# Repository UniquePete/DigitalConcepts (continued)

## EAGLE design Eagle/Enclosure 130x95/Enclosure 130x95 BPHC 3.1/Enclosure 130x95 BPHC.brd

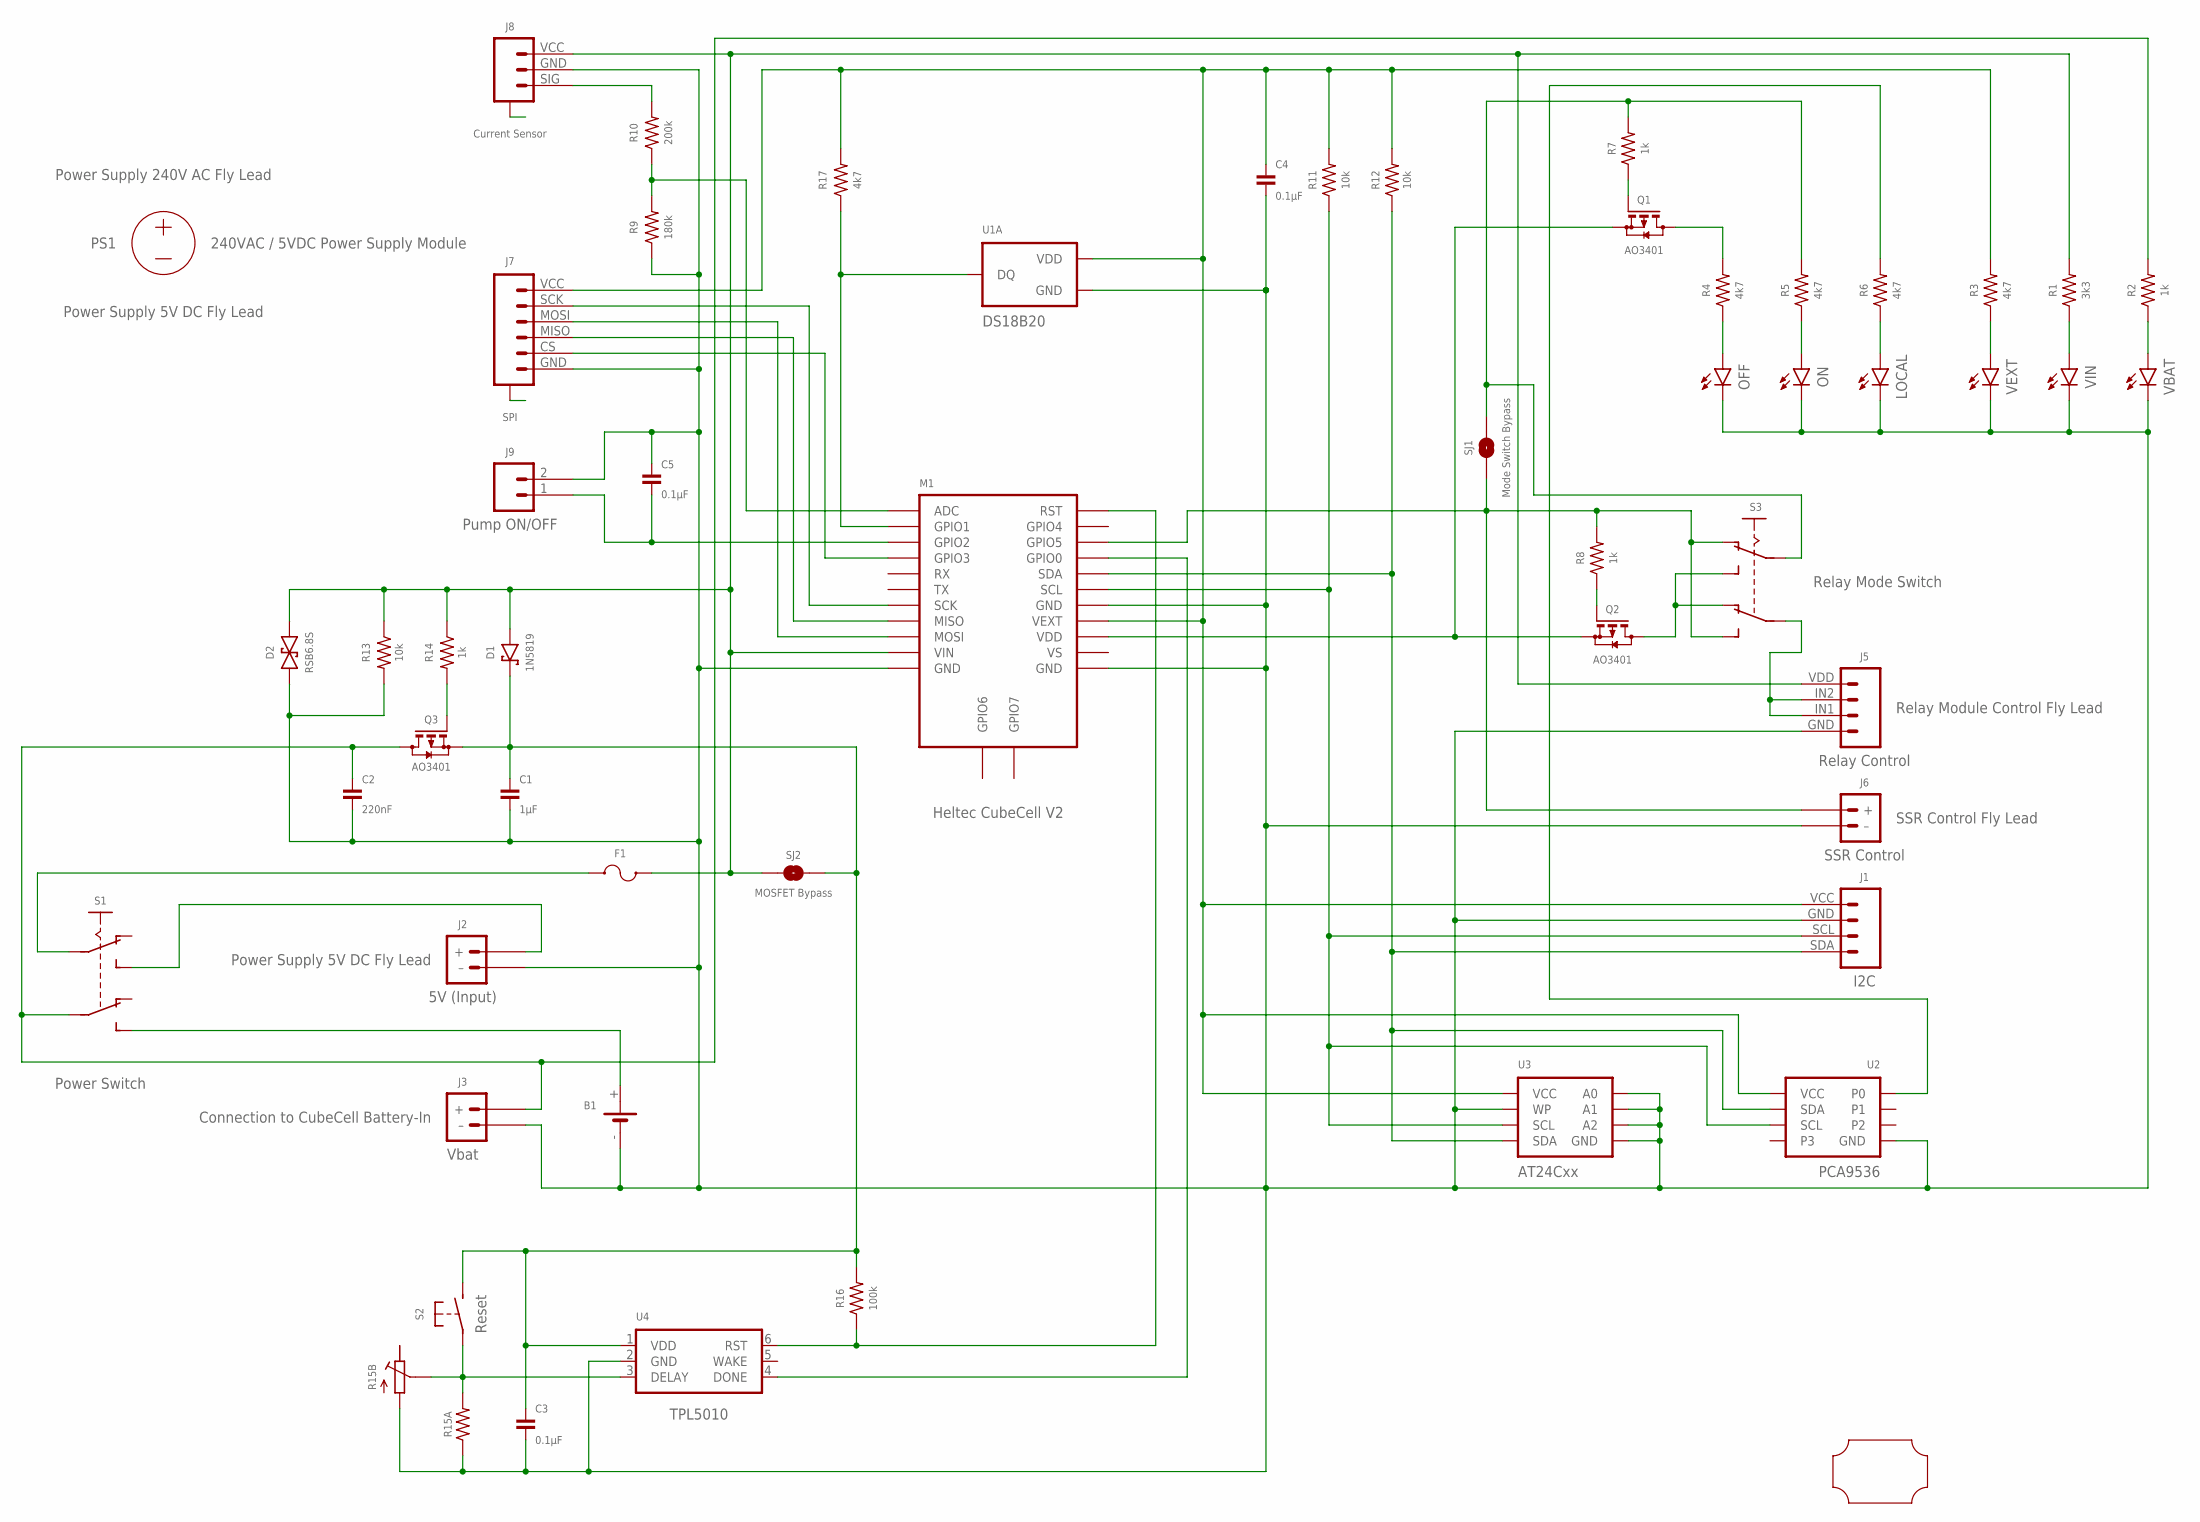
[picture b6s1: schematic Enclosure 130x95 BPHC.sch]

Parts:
B1: BATTERY-HOLDER-14500(AA); BATTERY-14500
C1: 1µF; C0805
C2: 220nF; C0805
C3, C4, C5: 0.1µF; C0805
D1: 1N5819; SOD-123
D2: RSB6.8S; VMD2
F1: Fuse; F0805
J1: I2C; CONN_04-I2C
J2: 5V (Input); JST-PH2.0-2-VERTICAL-POWER
J3: Vbat; JST-GH1.25-2-HORIZONTAL
J5: Relay Control; JST-PH2.0-4-HORIZONTAL-RELAY
J6: SSR Control; JST-PH2.0-2-HORIZONTAL-POWER
J7: SPI; JST-SH1.0-6-HORIZONTAL-SPI
J8: Current Sensor; JST-SH1.0-3-HORIZONTAL-SIG
J9: Pump ON/OFF; CONN_02-GENERIC
LOCAL: LEDCHIP-LED0805; CHIP-LED0805
M1: Heltec CubeCell V2; HELTEC-CUBECELL
OFF: LEDCHIP-LED0805; CHIP-LED0805
ON: LEDCHIP-LED0805; CHIP-LED0805
PCB1: PCB-OUTLINE-130X95-HALF-TOP; PROTO-130X95-OUTLINE-HALF-TOP
PS1: 240VAC / 5VDC Power Supply Module; AC_DC_POWER_SUPPLY
Q1, Q2, Q3: AO3401; SOT-23
R1: 3k3; R0805
R2, R7, R8, R14: 1k; R0805
R3, R4, R5, R6, R17: 4k7; R0805
R9: 180k; R0805
R10: 200k; R0805
R11, R12, R13: 10k; R0805
R15A: RESISTORR0805; R0805
R15B: RESISTOR-TRIMM-33; RTRIM3*3
R16: 100k; R0805
S1: Power Switch; SWITCH-DPDT-PTH
S2: Reset; SWITCH-2-PAD
S3: Relay Mode Switch; SWITCH-DPDT-SMD
SJ1: Mode Switch Bypass; SJ
SJ2: MOSFET Bypass; SJ
U1A: DS18B20; TO-92
U2: PCA9536; SOP-8
U3: AT24Cxx; SOP-8
U4: TPL5010; SOT-23-6
VBAT: LEDCHIP-LED0805; CHIP-LED0805
VEXT: LEDCHIP-LED0805; CHIP-LED0805
VIN: LEDCHIP-LED0805; CHIP-LED0805

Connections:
A6: J8.A@1 (A), J8.A@3 (A)
A8: J7.A@1 (A), J7.A@6 (A)
GND: B1.-, C1.2, C2.2, C3.2, C4.2, C5.1, D2.P$2 (2), J1.GND (2), J2.- (–), J3.- (–), J5.GND (4), J6.- (–), J7.GND (1), J8.GND (2), J9.2, LOCAL.C, M1.GND@11 (GND), M1.GND@14 (GND), M1.GND@18 (GND), OFF.C, ON.C, R9.1, R13.2, R15A.1, R15B.1 (A), U1A.1 (GND), U2.4 (GND), U3.1 (A0), U3.2 (A1), U3.3 (A2), U3.4 (GND), U3.7 (WP), U4.2 (GND), VBAT.C, VEXT.C, VIN.C
unnamed: R6.2, U2.1 (P0)
unnamed: B1.+, S1.P$6 (S2)
unnamed: C5.2, J9.1, M1.GPIO2
unnamed: C4.1, J1.VCC (1), J7.VCC (6), M1.VEXT, R3.2, R11.2, R12.2, R17.2, U1A.3 (VDD), U2.8 (VCC), U3.8 (VCC)
unnamed: J1.SDA (4), M1.SDA, R12.1, U2.7 (SDA), U3.5 (SDA)
unnamed: C1.1, C3.1, D1.C, Q3.2 (S), R16.2, S2.P$2 (S), SJ2.2, U4.1 (VDD)
unnamed: J6.+, M1.GPIO5, R8.2, S3.P$1 (O1), S3.P$6 (S2), SJ1.1
unnamed: M1.GPIO1, R17.1, U1A.2 (DQ)
unnamed: J1.SCL (3), M1.SCL, R11.1, U2.6 (SCL), U3.6 (SCL)
unnamed: R2.1, VBAT.A
unnamed: M1.GPIO0, U4.4 (DONE)
unnamed: OFF.A, R4.1
unnamed: R1.1, VIN.A
unnamed: R3.1, VEXT.A
unnamed: F1.2, S1.P$2 (P1)
unnamed: J2.+, S1.P$3 (S1)
unnamed: Q1.3 (D), R4.2
unnamed: M1.ADC, R9.2, R10.1
unnamed: ON.A, R5.1
unnamed: LOCAL.A, R6.1
unnamed: D1.A, D2.P$1 (1), F1.1, J5.VDD (1), J8.VCC (3), M1.VIN, R1.2, R13.1, R14.1, SJ2.1
unnamed: Q1.1 (G), R7.1
unnamed: Q2.3 (D), S3.P$3 (S1), S3.P$4 (O2)
unnamed: Q2.1 (G), R8.1
unnamed: J8.SIG (1), R10.2
unnamed: R5.2, R7.2, S3.P$2 (P1), SJ1.2
unnamed: J5.IN1 (3), J5.IN2 (2), S3.P$5 (P2)
unnamed: J7.SCK (5), M1.SCK
unnamed: J7.MOSI (4), M1.MOSI
unnamed: J7.MISO (3), M1.MISO
unnamed: J7.CS (2), M1.GPIO3
unnamed: C2.1, J3.+, Q3.3 (D), R2.2, S1.P$5 (P2)
unnamed: R15A.2, R15B.2 (S), S2.P$1, U4.3 (DELAY)
unnamed: M1.RST, R16.1, U4.6 (RST)
unnamed: Q3.1 (G), R14.2
VCC: M1.VDD, Q1.2 (S), Q2.2 (S)

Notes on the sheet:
SSR Control Fly Lead
Power Supply 5V DC Fly Lead
Connection to CubeCell Battery-In
Power Supply 240V AC Fly Lead
Relay Module Control Fly Lead

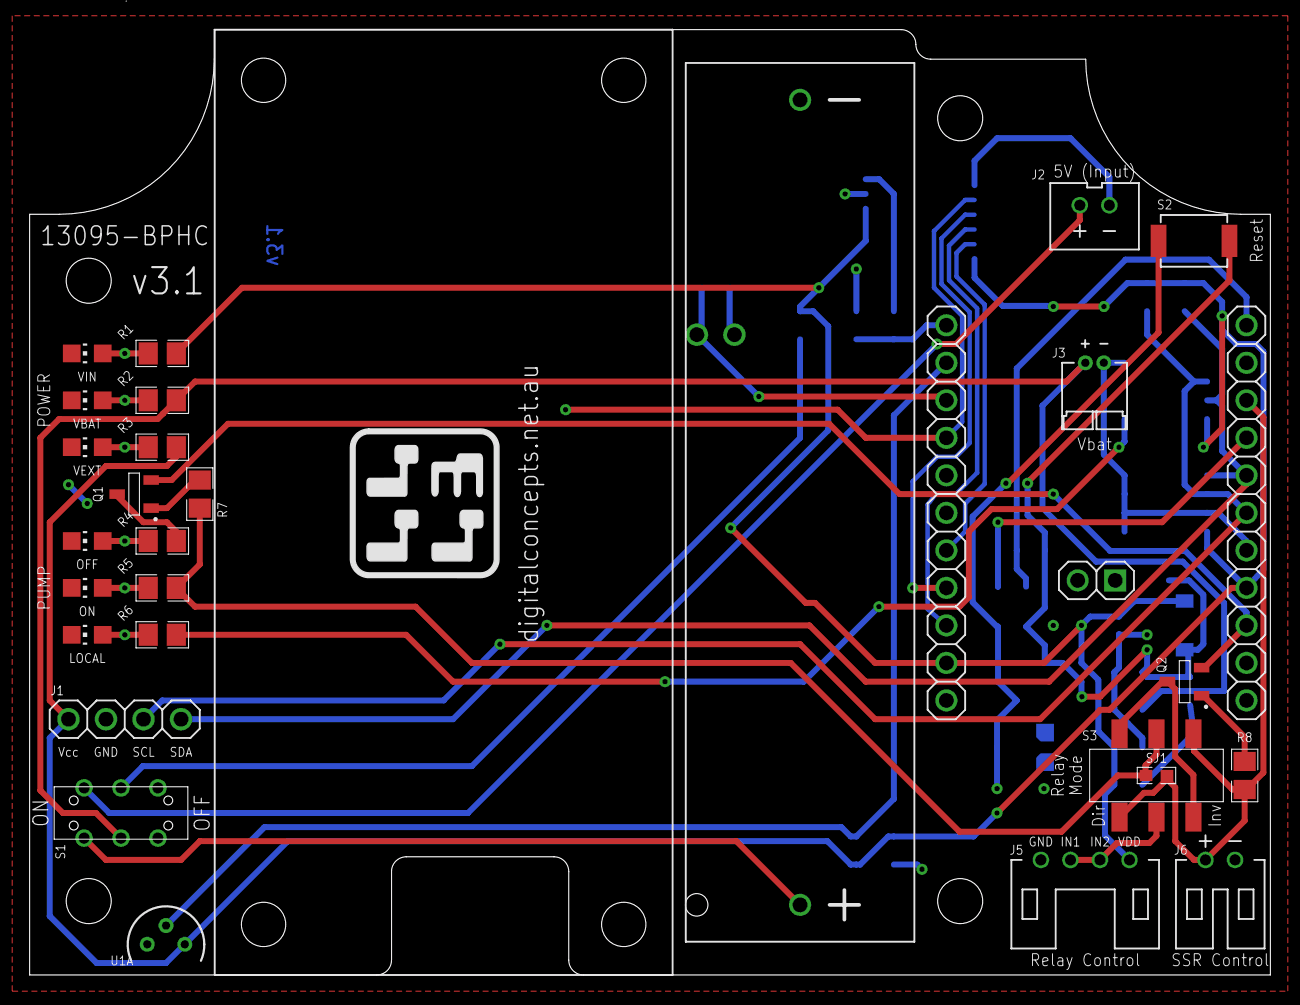
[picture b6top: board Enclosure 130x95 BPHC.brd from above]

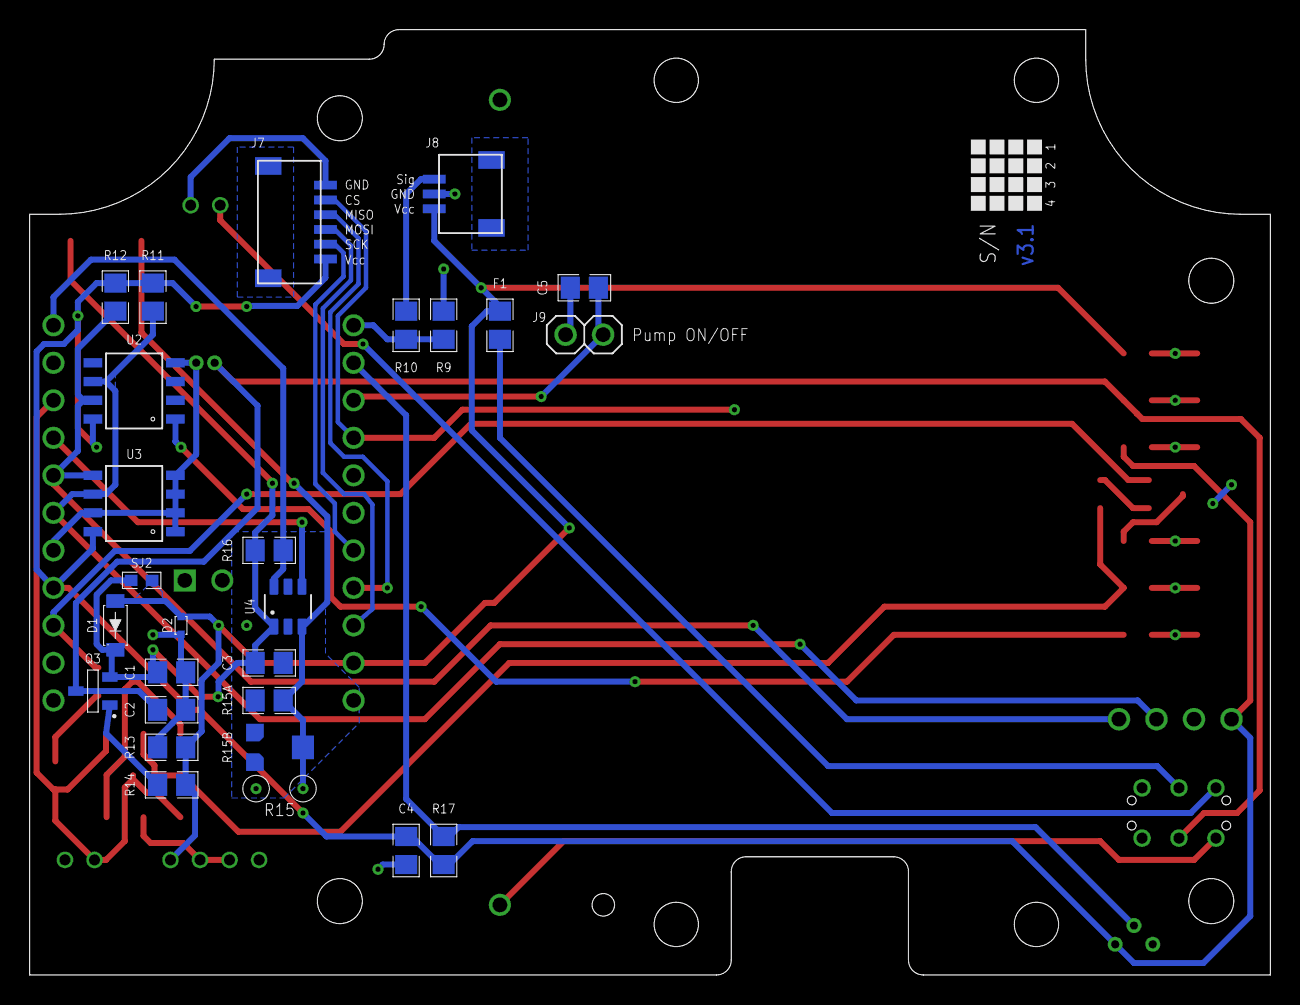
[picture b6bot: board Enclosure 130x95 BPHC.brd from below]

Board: 2 copper layers, 84.0 x 64.0 mm, 56 parts (26 on the bottom side), 39 nets.
